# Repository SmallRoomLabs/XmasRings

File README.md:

# XmasRings

These are cheap 10x10 cm PCBs that are routed/cut into seven rings holding a total of 45 LEDs with individual control using Charlieplexing with a PIC16F1705 microcontroller. There are a couple of different light pattern that it it cycling though.

Click image to play video from YouTube

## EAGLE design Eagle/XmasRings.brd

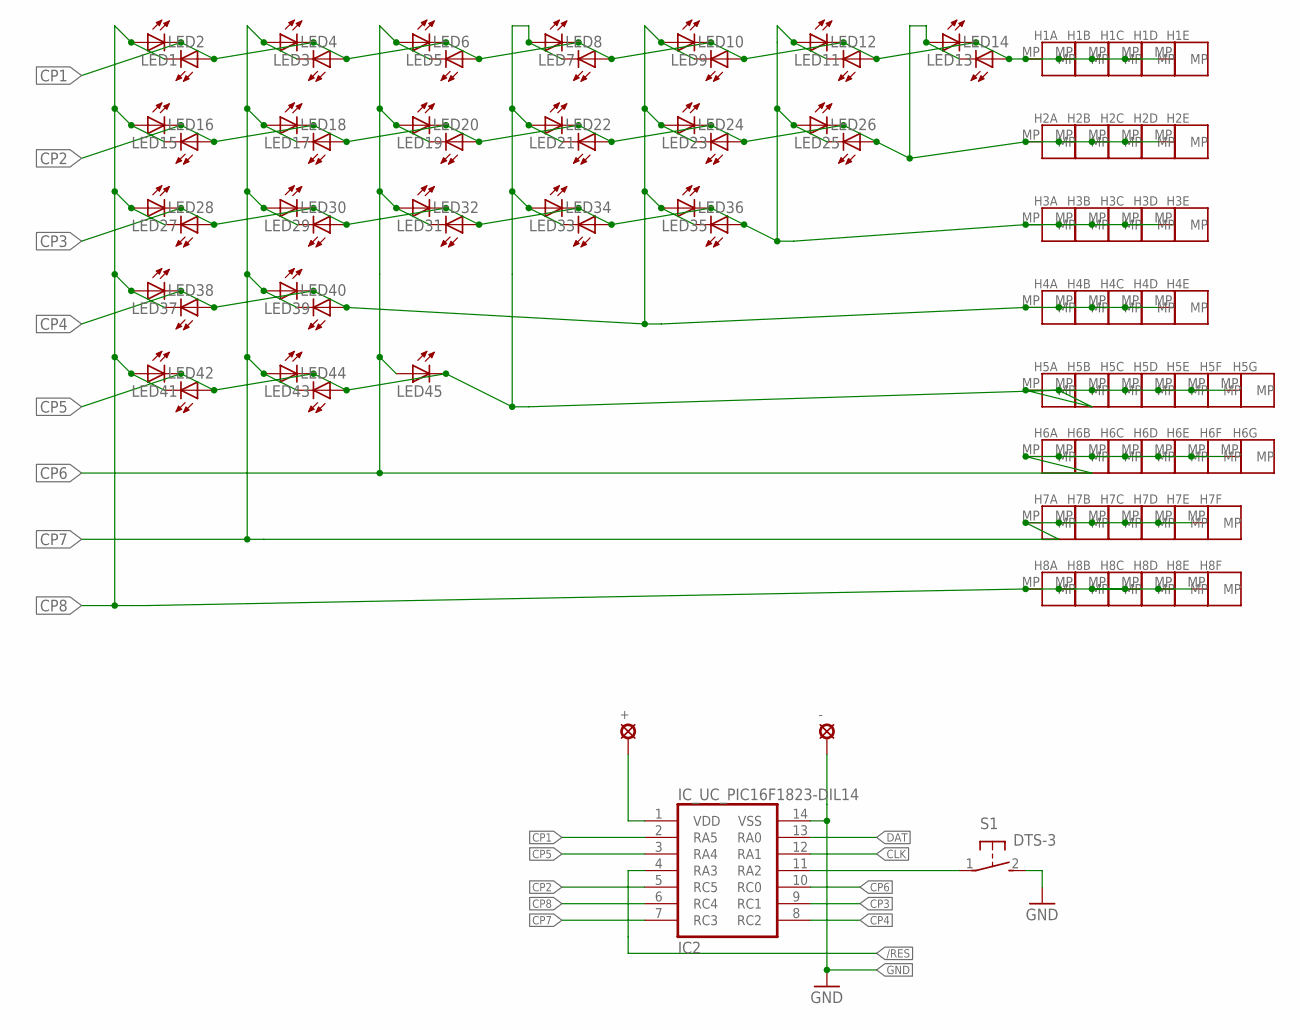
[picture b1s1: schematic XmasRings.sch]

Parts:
+: LSP10
-: LSP10
H1A, H1B, H1C, H1D, H1E, H2A, H2B, H2C, H2D, H2E, H3A, H3B, H3C, H3D, H3E, H4A, H4B, H4C, H4D, H4E, H5A, H5B, H5C, H5D, H5E, H5F, H5G, H6A, H6B, H6C, H6D, H6E, H6F, H6G, H7A, H7B, H7C, H7D, H7E, H7F, H8A, H8B, H8C, H8D, H8E, H8F: PADH08SS; PAD08SS
IC2: IC_UC_PIC16F1823-DIL14; DIP14
LED1, LED2, LED3, LED4, LED5, LED6, LED7, LED8, LED9, LED10, LED11, LED12, LED13, LED14, LED15, LED16, LED17, LED18, LED19, LED20, LED21, LED22, LED23, LED24, LED25, LED26, LED27, LED28, LED29, LED30, LED31, LED32, LED33, LED34, LED35, LED36, LED37, LED38, LED39, LED40, LED41, LED42, LED43, LED44, LED45: LED5SQ; 5MM-SQ
S1: DTS-3

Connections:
/RES: IC2.4 (RA3)
CLK: IC2.12 (RA1)
CP1: H1A.MP, H1B.MP, H1C.MP, H1D.MP, H1E.MP, IC2.2 (RA5), LED1.C, LED2.A, LED3.C, LED4.A, LED5.C, LED6.A, LED7.C, LED8.A, LED9.C, LED10.A, LED11.C, LED12.A, LED13.C, LED14.A
CP2: H2A.MP, H2B.MP, H2C.MP, H2D.MP, H2E.MP, IC2.5 (RC5), LED13.A, LED14.C, LED15.C, LED16.A, LED17.C, LED18.A, LED19.C, LED20.A, LED21.C, LED22.A, LED23.C, LED24.A, LED25.C, LED26.A
CP3: H3A.MP, H3B.MP, H3C.MP, H3D.MP, H3E.MP, IC2.9 (RC1), LED11.A, LED12.C, LED25.A, LED26.C, LED27.C, LED28.A, LED29.C, LED30.A, LED31.C, LED32.A, LED33.C, LED34.A, LED35.C, LED36.A
CP4: H4A.MP, H4B.MP, H4C.MP, H4D.MP, H4E.MP, IC2.8 (RC2), LED9.A, LED10.C, LED23.A, LED24.C, LED35.A, LED36.C, LED37.C, LED38.A, LED39.C, LED40.A
CP5: H5A.MP, H5B.MP, H5C.MP, H5D.MP, H5E.MP, H5F.MP, H5G.MP, IC2.3 (RA4), LED7.A, LED8.C, LED21.A, LED22.C, LED33.A, LED34.C, LED41.C, LED42.A, LED43.C, LED44.A, LED45.C
CP6: H6A.MP, H6B.MP, H6C.MP, H6D.MP, H6E.MP, H6F.MP, H6G.MP, IC2.10 (RC0), LED5.A, LED6.C, LED19.A, LED20.C, LED31.A, LED32.C, LED45.A
CP7: H7A.MP, H7B.MP, H7C.MP, H7D.MP, H7E.MP, H7F.MP, IC2.7 (RC3), LED3.A, LED4.C, LED17.A, LED18.C, LED29.A, LED30.C, LED39.A, LED40.C, LED43.A, LED44.C
CP8: H8A.MP, H8B.MP, H8C.MP, H8D.MP, H8E.MP, H8F.MP, IC2.6 (RC4), LED1.A, LED2.C, LED15.A, LED16.C, LED27.A, LED28.C, LED37.A, LED38.C, LED41.A, LED42.C
DAT: IC2.13 (RA0)
GND: -.MP, IC2.14 (VSS), S1.2
unnamed: IC2.11 (RA2), S1.1
VCC: +.MP, IC2.1 (VDD)

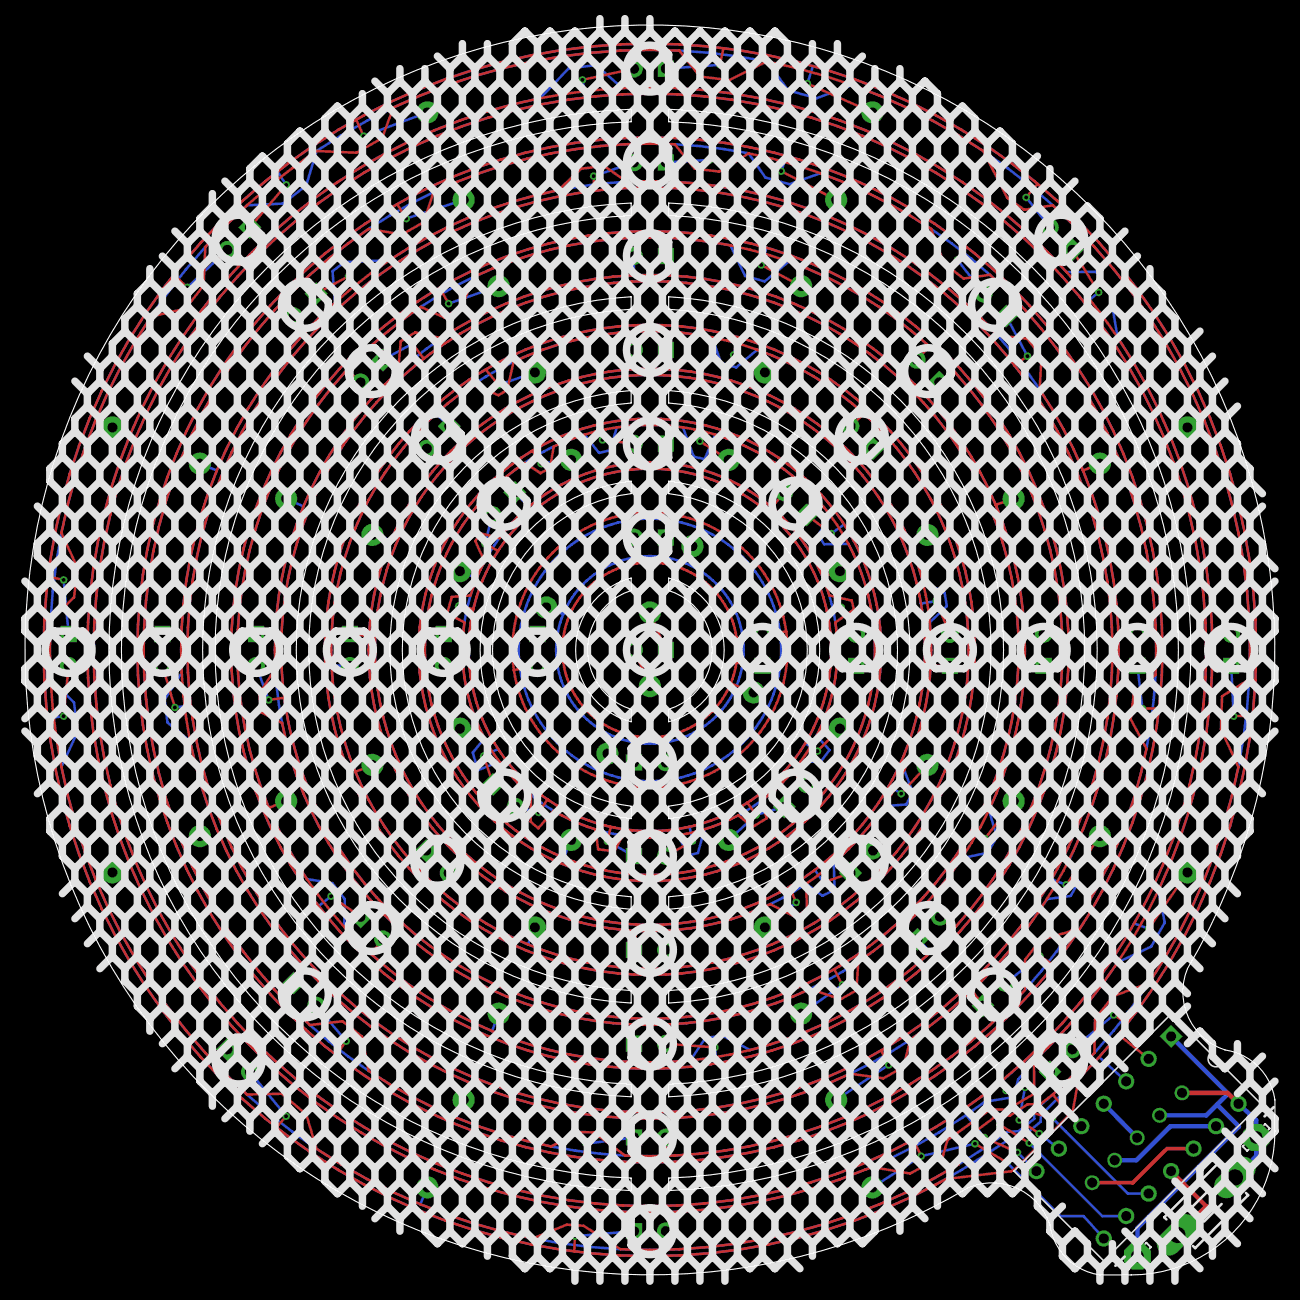
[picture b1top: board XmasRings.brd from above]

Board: 2 copper layers, 100.0 x 100.0 mm, 95 parts (0 on the bottom side), 11 nets.

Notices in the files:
parts and their libraries:
SmallRoomLabs_Misc: Copyright(c) Mats Engstrom - mats@smallroomlabs.com
SmallRoomLabs_Misc: Creative Commons Attribution-ShareAlike 4.0 (CC BY-SA 4.0)
